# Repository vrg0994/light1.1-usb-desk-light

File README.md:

# Light 1.1 - USB-C Desk Light

A compact, custom-designed USB-C powered LED desk light. This was my first project focused on USB-C power negotiation and parallel component routing.

## 📝 Project Overview
This board takes 5V from any standard USB-C charger and powers 5 white LEDs. It features a physical slide switch for on/off control and uses the standard 5.1kΩ CC resistor configuration to ensure modern smart chargers output power.

## ⚙️ Technical Specifications
*   **Input:** USB-C (5V)
*   **Power Draw:** ~150mA (5 LEDs @ ~30mA each)
*   **Connector:** 16-Pin USB-C Receptacle
*   **Switch:** DPDT Slide Switch (SMD)
*   **Board Layers:** 2-Layer (Top Copper only used for routing)
*   **Dimensions:** [Insert your exact board dimensions here, e.g., 25mm x 20mm]

## 📁 Repository Structure
*   **`/Hardware`**: KiCad schematic (`.kicad_sch`) and PCB layout (`.kicad_pcb`) source files.
*   **`/Gerbers`**: Manufacturing ZIP file (ready for JLCPCB).
*   **`/Images`**: 3D renders and DRC (Design Rules Check) screenshots.

## 🛠️ Design Details & Lessons Learned
*   **USB-C Handshake:** Integrated 5.1kΩ pull-down resistors on CC1 and CC2 to unlock 5V from smart chargers.
*   **Current Limiting:** Each LED is paired with a 68Ω resistor to limit current to ~29mA, preventing burnout.
*   **The "Ladder" Routing:** Learned how to properly route parallel components by separating the 5V rail and the Ground rail to avoid accidental short circuits.
*   **Design Verification:** Passed DRC with 0 Errors and 0 Unconnected Items.

## 🖼️ Design Gallery

*(Note: Ensure the image filename matches your uploaded file)*

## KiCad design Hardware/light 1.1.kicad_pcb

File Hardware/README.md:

This folder contains the KiCad source files for light1.1

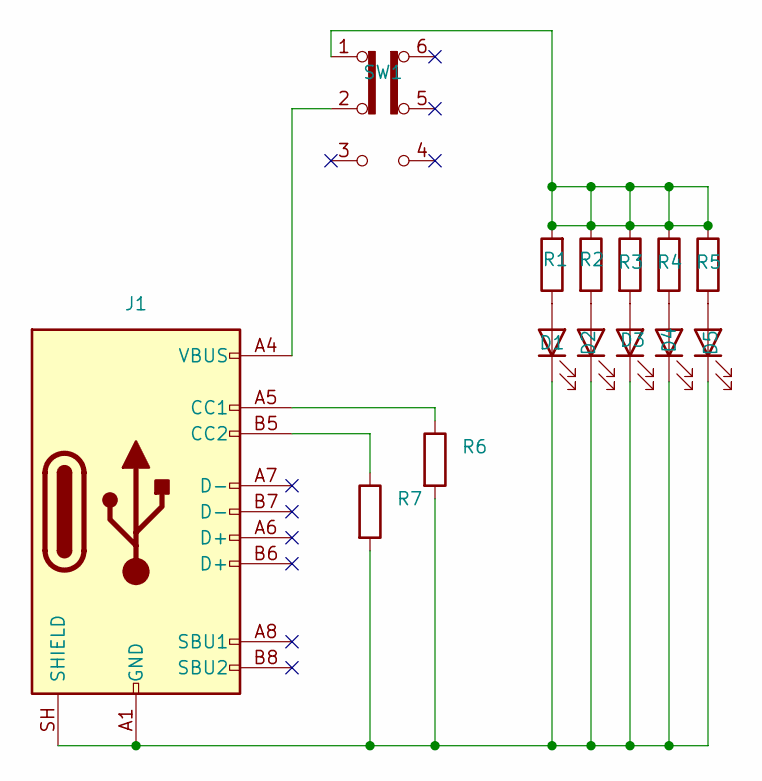
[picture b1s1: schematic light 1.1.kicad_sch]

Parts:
D1, D2, D3, D4, D5: LED; LED_0805_2012Metric
J1: USB_C_Receptacle_USB2.0_16P; USB_C_Receptacle_GCT_USB4105-xx-A_16P_TopMnt_Horizontal
R1, R2, R3, R4, R5: 68; R_0805_2012Metric
R6, R7: 5.1k; R_0805_2012Metric
SW1: SW_Slide_DPDT; SW_CK_JS202011CQN_DPDT_Straight

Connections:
unnamed: D1.2 (A), R1.1
unnamed: D1.1 (K), D2.1 (K), D3.1 (K), D4.1 (K), D5.1 (K), J1.A1 (GND), J1.A12 (GND), J1.B1 (GND), J1.B12 (GND), J1.SH (SHIELD), R6.2, R7.2
unnamed: D2.2 (A), R2.2
unnamed: D3.2 (A), R3.2
unnamed: D4.2 (A), R4.2
unnamed: D5.2 (A), R5.2
unnamed: J1.A5 (CC1), R6.1
unnamed: J1.B5 (CC2), R7.1
unnamed: J1.A4 (VBUS), J1.A9 (VBUS), J1.B4 (VBUS), J1.B9 (VBUS), SW1.2 (B)
unnamed: R1.2, R2.1, R3.1, R4.1, R5.1, SW1.1 (A)

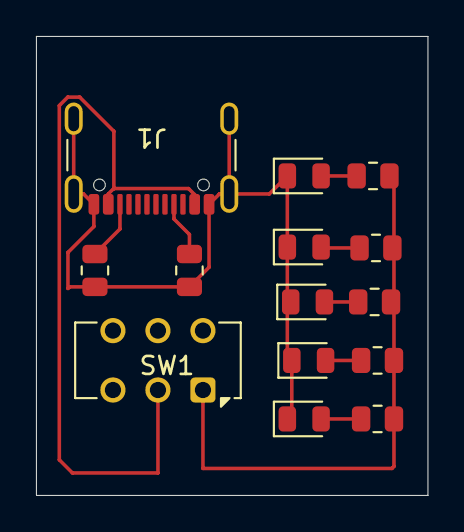
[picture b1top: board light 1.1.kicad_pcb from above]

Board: 2 copper layers, 21.8 x 25.5 mm, 14 parts (0 on the bottom side), 10 nets.
